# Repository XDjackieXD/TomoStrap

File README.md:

# TomoStrap
 
 The code residing in the "microcontroller" and "pebble" directories was written by me, Jakob (Jack/XDjackieXD), as part of the diploma thesis you are required to do for your A Level at a higher technical school in Austria.
 The KiCAD files inside the "hardware" directory, designed by Jakob Z., represent the hardware the aforementioned code runs on.
 
 ## Introduction
 
 The main topic of the diploma thesis was to build a device similar to http://chrisharrison.net/projects/tomo/tomo.pdf while increasing mobility by using a Pebble smartwatch as the base.
 During development I snuck in a MAX30102 pulseoximeter which basically is the main feature as of now.
 
 ## Usage
 
 ### Microcontroller Firmware
 
 To compile the Firmware for the KL03 ARM processor, it'll be the easiest route to install the kinetis design studio. The hardware abstraction layer was generated using NXP's MCUXpresso tool.
 Most parts of the code are written in a way that should allow for fairly easy porting to other microcontroller platforms.
 Currently the handlers for data received are inside the library. Changing this to callbacks should be easy though.
 The firmware isn't complete by any means but contineous SpO2 and pulse measurements are working as intended. Things that need to be addressed before "production" use include proper power management and automatic gain control for the MAX30102's LEDs and configurable ADC ranges as those values are currently hard coded which lead to unreliable measurements in many situations.
 
 ### Pebble App
 
 The included pebble app is able to display any SpO2 and pulse data sent by the microcontroller. Impedance data is currently only printed into the debug log of the Pebble app.
 
 ## License
 
 All code written by me and the SpO2 calculation library is licensed under the MIT license (LICENSE-software.txt).
 The dstring library used for SpO2 debugging using FlexiPlot is licensed under the Creative Commons license (LICENSE-dstring.txt).
 All other source code files included in the microcontroller firmware directory (everything not inside of the "source" directory) is licensed under the respective licenses stated in the source file headers.

 The hardware is Licensed under the terms of the Creative Commons Attribution Sharealike 4.0 license (LICENSE-hardware.txt) with the exception of the kicad library by Michael Cousins which is licensed under the terms of the Creative Commons Attribution Sharealike 3.0 Unported license (LICENSE-kicad-libs.txt).

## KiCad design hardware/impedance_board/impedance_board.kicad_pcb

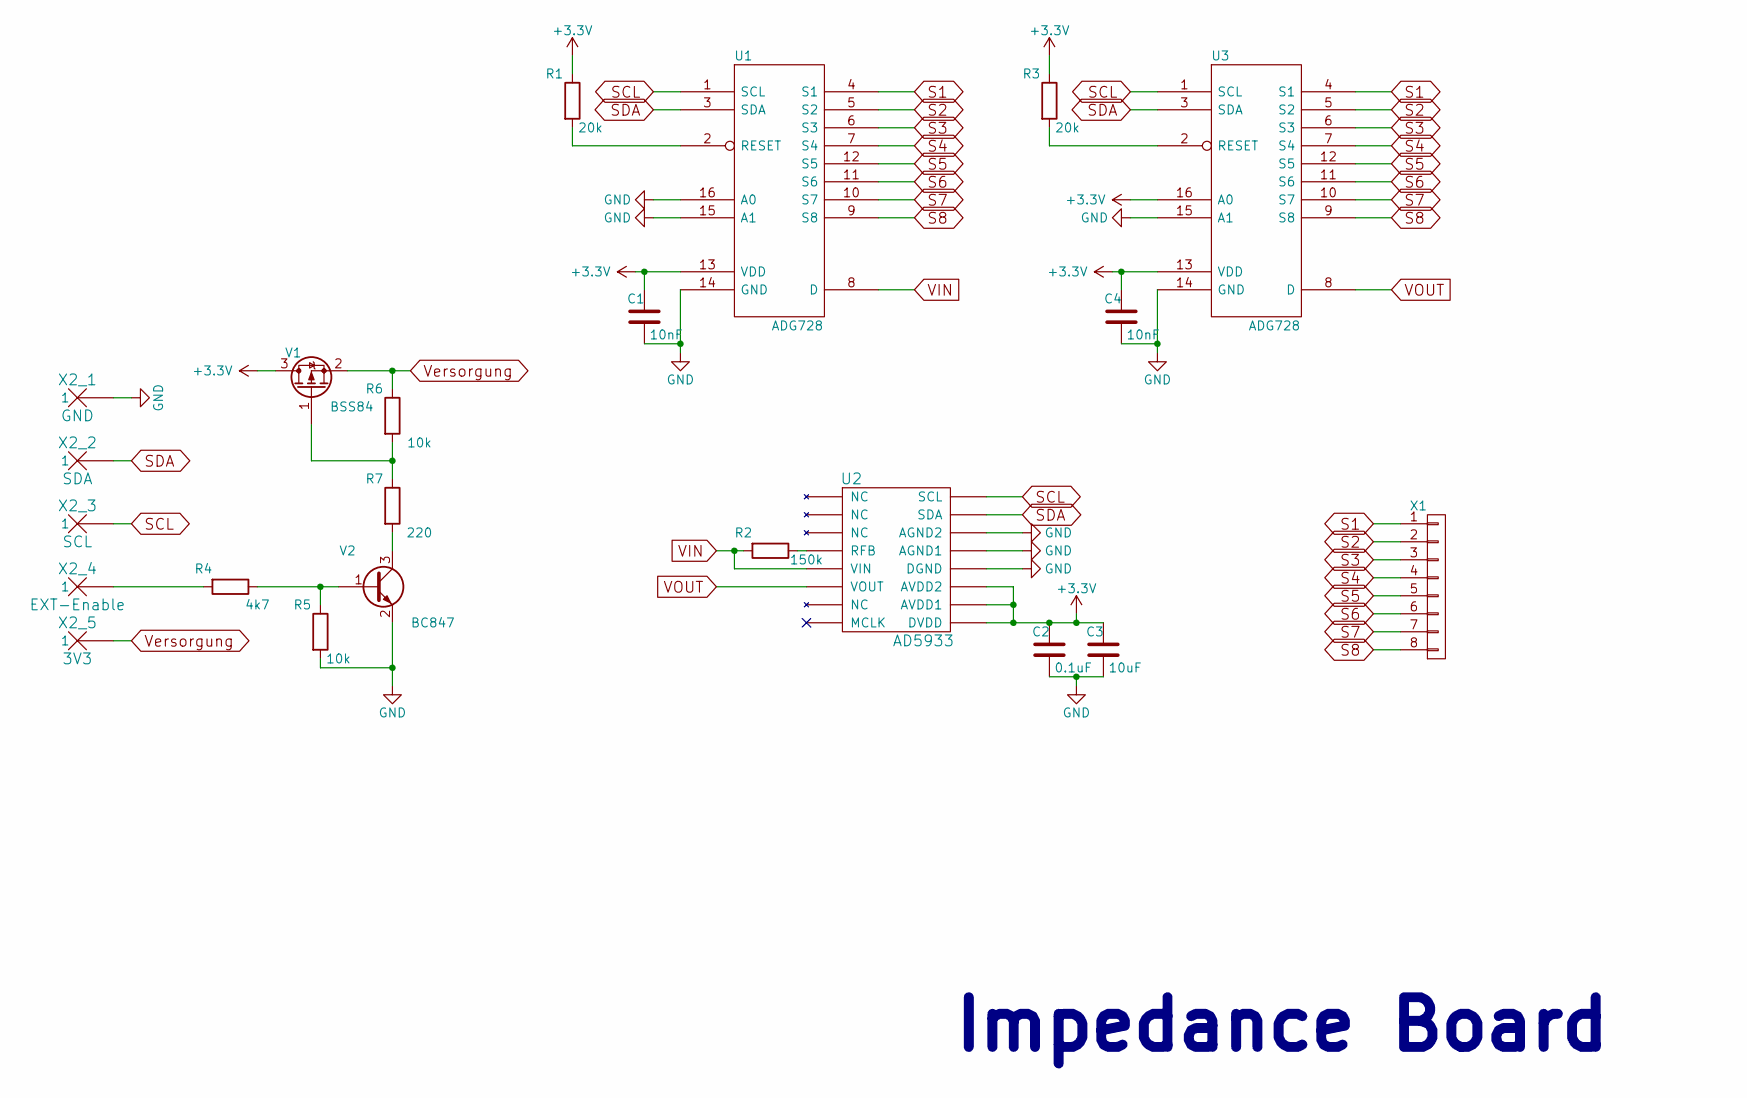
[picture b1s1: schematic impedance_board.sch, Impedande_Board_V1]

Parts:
C1, C4: 10nF; C_0805_HandSoldering
C2: 0.1uF; C_0805_HandSoldering
C3: 10uF; C_1206_HandSoldering
R1, R3: 20k; R_0805_HandSoldering
R2: 150k; R_0805_HandSoldering
R4: 4k7; R_0805_HandSoldering
R5, R6: 10k; R_0805_HandSoldering
R7: 220; R_0805_HandSoldering
U1, U3: ADG728; TSSOP16
U2: AD5933; SSOP16
V1: BSS84; SOT-23_Handsoldering
V2: BC847; SOT-23_Handsoldering
X1: CONN_01X08; JST_GH_SM08B-GHS-TB_08x1.25mm_Angled
X2_1: GND; 1Pin
X2_2: SDA; 1Pin
X2_3: SCL; 1Pin
X2_4: EXT-Enable; 1Pin
X2_5: 3V3; 1Pin

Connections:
+3V3: C1.1, C2.1, C3.1, C4.1, R1.1, R3.1, U1.13 (VDD), U2.9 (DVDD), U2.10 (AVDD1), U2.11 (AVDD2), U3.13 (VDD), U3.16 (A0), V1.3 (D)
GND: C1.2, C2.2, C3.2, C4.2, R5.2, U1.14 (GND), U1.15 (A1), U1.16 (A0), U2.12 (DGND), U2.13 (AGND1), U2.14 (AGND2), U3.14 (GND), U3.15 (A1), V2.2 (E), X2_1.1
unnamed: R1.2, U1.2 (RESET)
unnamed: R2.1, U2.4 (RFB)
unnamed: R3.2, U3.2 (RESET)
unnamed: R4.1, R5.1, V2.1 (B)
unnamed: R4.2, X2_4.1
unnamed: R6.2, R7.1, V1.1 (G)
unnamed: R7.2, V2.3 (C)
S1: U1.4 (S1), U3.4 (S1), X1.1
S2: U1.5 (S2), U3.5 (S2), X1.2
S3: U1.6 (S3), U3.6 (S3), X1.3
S4: U1.7 (S4), U3.7 (S4), X1.4
S5: U1.12 (S5), U3.12 (S5), X1.5
S6: U1.11 (S6), U3.11 (S6), X1.6
S7: U1.10 (S7), U3.10 (S7), X1.7
S8: U1.9 (S8), U3.9 (S8), X1.8
SCL: U1.1 (SCL), U2.16 (SCL), U3.1 (SCL), X2_3.1
SDA: U1.3 (SDA), U2.15 (SDA), U3.3 (SDA), X2_2.1
VIN: R2.2, U1.8 (D), U2.5 (VIN)
VOUT: U2.6 (VOUT), U3.8 (D)
Versorgung: R6.1, V1.2 (S), X2_5.1

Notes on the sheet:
Impedance Board

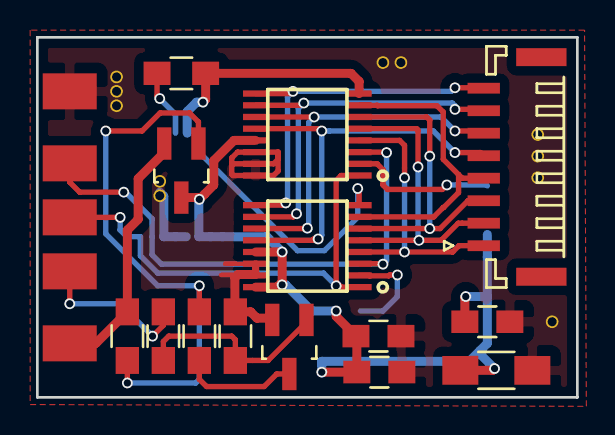
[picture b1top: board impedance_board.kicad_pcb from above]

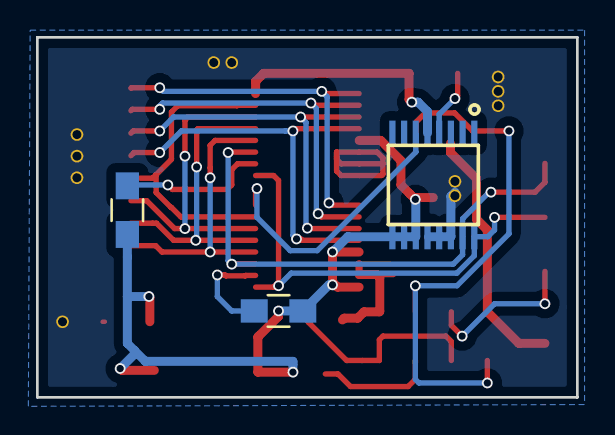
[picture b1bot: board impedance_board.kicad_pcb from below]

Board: 2 copper layers, 30.0 x 20.0 mm, 22 parts (3 on the bottom side), 22 nets.

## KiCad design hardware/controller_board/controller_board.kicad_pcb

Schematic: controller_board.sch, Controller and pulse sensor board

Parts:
C1: 10µ; A_3216-18R; mouser 77-VJ1206V106ZXQTBC
C2: 4.7µ; A_3216-18R; mouser 77-VJ1206V475MXJTBC
C3: 10n; C0805; mouser 710-885012207066
C4: 1µ; A_3216-18R; mouser 77-VJ1206Y105MXJTBC
C5: 100n; C0805; mouser 710-885012207072
EXT-ENABLE12: SMD1_27-2_54
EXT-GND12: SMD1_27-2_54
EXT-SCL12: SMD1_27-2_54
EXT-SDA12: SMD1_27-2_54
EXT-VCC12: SMD1_27-2_54
IC1: LP2985; TI-LP2985; mouser 595-LP2985-33DBVR
IC2: 74LVC1G07DBV; SOT23-5; mouser 595-SN74LVC1G07DBVR
IC3: MAX30102EFD+; MAXIM-MAX30100; mouser 700-MAX30102EFD+
PEBBLE-DATA12: SMD1_27-2_54
PEBBLE-GND1, PEBBLE-GND2: SMD1_27-2_54
PEBBLE-VCC12: SMD1_27-2_54
R1, R2, R3, R4: 4k7; M0805; mouser 667-ERJ-6GEYJ472V
R5: 10k; M0805; mouser 667-ERJ-6ENF1003V
SWD-CLK12: TPB1,27; B1_27
SWD-DIO12: TPB1,27; B1_27
SWD-GND12: TPB1,27; B1_27
SWD-RESET12: TPB1,27; B1_27
U1: MKL03Z32VFG4; 98ASA00525D; mouser 841-MKL03Z32VFG4
V1, V2: ESDA6V1L; SOT-23; mouser 511-ESDA6V1L
VP_0, VP_1, VP_2, VP_3, VP_4, VP_5, VP_6, VP_7, VP_8, VP_9, VP_10, VP_11: VPDEV0; VPAC0

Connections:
3V3: C1.+, C4.+, C5.1, EXT-VCC12.1, IC1.1 (VIN), IC2.5 (VCC), IC3.9 (R_LED+), IC3.10 (IR_LED+), PEBBLE-VCC12.1, R1.2, R2.2, R3.2, R4.2, R5.2, U1.1 (VDD), V1.2; also elsewhere on the board
/1.8ON: IC1.3 (ON/OFF), R4.1, U1.9 (PTB1/IRQ_6)
/EXT-ENABLE: EXT-ENABLE12.1, U1.13 (PTB5/IRQ_12)
/INT: IC3.13 (INT), R3.1, U1.10 (PTB2/IRQ_7)
/N$1: C3.1, IC1.4 (BYPASS)
/N$3: C2.+, IC1.5 (VOUT), IC3.11 (VDD)
/RESET: SWD-RESET12.TP, U1.15 (PTA1/IRQ_1/LPTMR0_ALT1)
/RX: IC2.4 (O), PEBBLE-DATA12.1, R5.1, U1.4 (PTA4), V1.1; also elsewhere on the board
/SCL: EXT-SCL12.1, IC3.2 (SCL), R2.1, U1.11 (PTB3/IRQ_10), V2.1; also elsewhere on the board
/SDA: EXT-SDA12.1, IC3.3 (SDA), R1.1, U1.12 (PTB4/IRQ_11), V2.2; also elsewhere on the board
/SWD-CLK: SWD-CLK12.TP, U1.14 (PTA0/IRQ_0/LLWU_P7)
/SWD-DIO: SWD-DIO12.TP, U1.16 (PTA2)
/TX: IC2.2 (I), U1.3 (PTA3)
GND: C1.-, C2.-, C3.2, C4.-, C5.2, EXT-GND12.1, IC1.2 (GND), IC2.3 (GND), IC3.4 (PGND), IC3.12 (GND), PEBBLE-GND1.1, PEBBLE-GND2.1, SWD-GND12.TP, U1.2 (VSS), U1.17 (EPAD), V1.3, V2.3, VP_0.VP, VP_1.VP, VP_2.VP, VP_3.VP, VP_4.VP, VP_5.VP, VP_6.VP, VP_7.VP, VP_8.VP, VP_9.VP, VP_10.VP, VP_11.VP; also elsewhere on the board

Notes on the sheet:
IC3
MAX30102
Controller Board

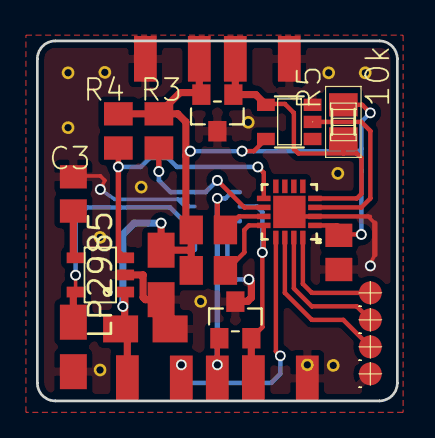
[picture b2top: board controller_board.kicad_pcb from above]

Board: 2 copper layers, 20.0 x 20.0 mm, 42 parts (0 on the bottom side), 14 nets.

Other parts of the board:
D1, D2: ESDA6V1L; SOT-23
VP_10#2: VPDEV0; VPAC0

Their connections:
3V3: D1.2; also elsewhere on the board
/RX: D1.1; also elsewhere on the board
/SCL: D2.1; also elsewhere on the board
/SDA: D2.2; also elsewhere on the board
GND: D1.3, D2.3, VP_10#2.VP; also elsewhere on the board
